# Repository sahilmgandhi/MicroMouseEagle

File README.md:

# MicroMouseEagle

MicroMouse eagle schematic and PCB Design for 2017 -> Sahil, Kyle, Vansh

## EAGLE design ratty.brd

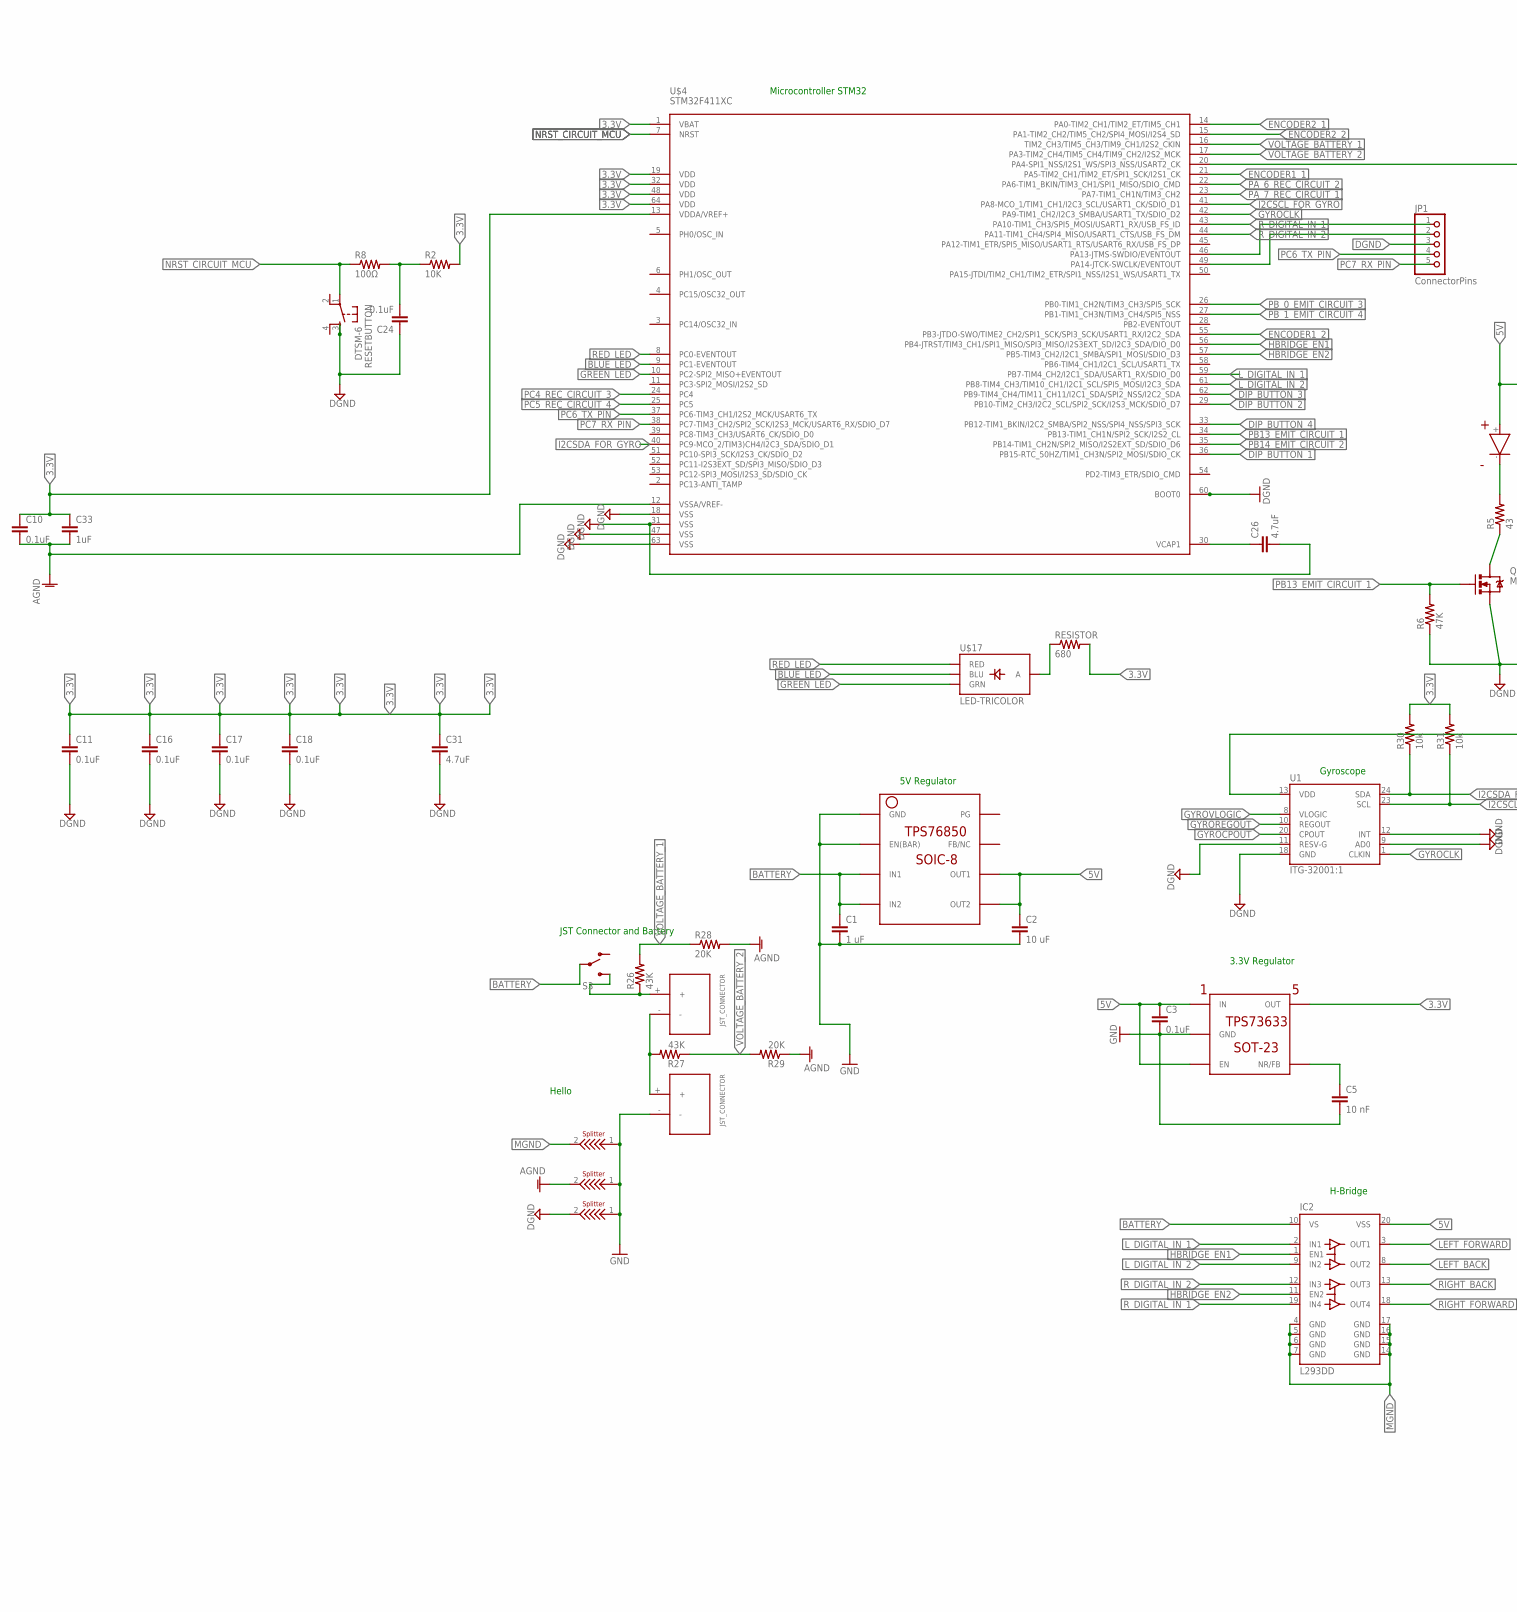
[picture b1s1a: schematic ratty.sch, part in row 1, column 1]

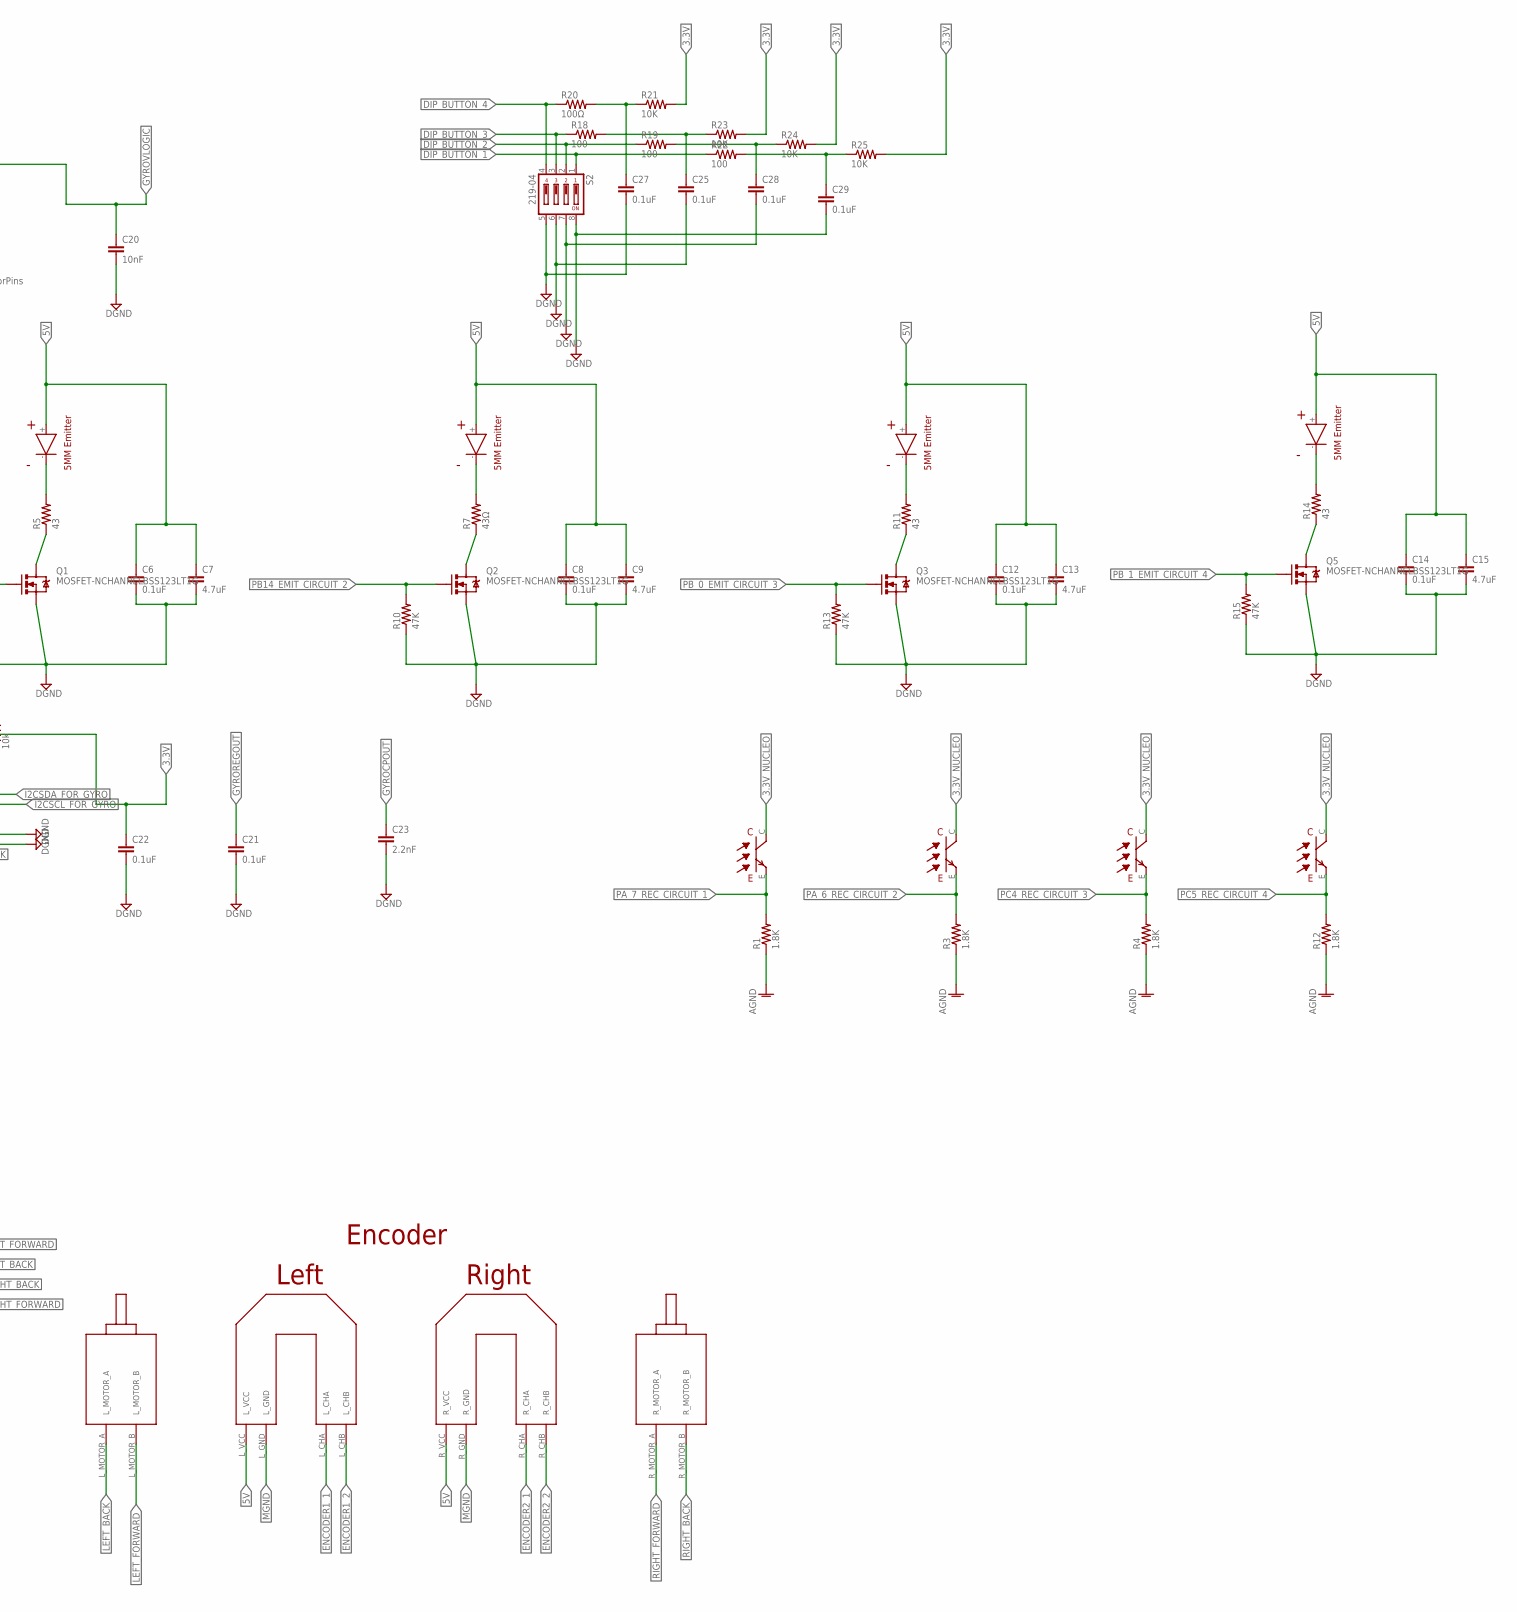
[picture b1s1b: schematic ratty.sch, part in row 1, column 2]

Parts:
A_SPLITTER: SPLITTER
C1: 1 uF; C0603
C2: 10 uF; C0603
C3, C6, C8, C10, C11, C12, C14, C16, C17, C18, C21, C22, C24, C25, C27, C28, C29: 0.1uF; C0603
C5: 10 nF; C0603
C7, C9, C13, C15, C26, C31: 4.7uF; C0603
C20: 10nF; C0603
C23: 2.2nF; C0603
C33: 1uF; C0603
D_SPLITTER: SPLITTER
IC2: L293DD; SO20
JP1: ConnectorPins; 1X05
M_SPLITTER: SPLITTER
Q1, Q2, Q3, Q5: MOSFET-NCHANNELBSS123LT1G; SOT23-3
R1, R3, R4, R12: 1.8K; R0603
R2, R21, R23, R24, R25: 10K; R0603
R5, R11, R14: 43; R1206
R6, R10, R13, R15: 47K; R0603
R7: 43Ω; R1206
R8, R20: 100Ω; R0603
R18, R19, R22: 100; R0603
R26, R27: 43K; R0603
R28, R29: 20K; R0603
R30, R31: 10k; R0603
RESETBUTTON: DTSM-6
RESISTOR: 680; R0603
S2: 219-04; CTS-219-04
S3: SWITCH-SPSTPTH; SWITCH-SPDT
U1: ITG-32001:1; QFN-24_ITG3200_1:1
U$1, U$2: JST_CONNECTOR_FEMALE
U$3: TPS76850(SOIC-8)
U$4: STM32F411XC; LQFP64
U$5: TPS73633(SOT-23)
U$6, U$9, U$11, U$13: RECEIVER
U$8: FUTURA_V1.0_MOTOR_MOUNT; FUTURA_V1.0_MOTOT_MOUNT
U$15, U$16, U$18, U$19: EMITTER
U$17: LED-TRICOLOR; LED-TRICOLOR-SMD

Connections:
3.3V: C10.1, C11.1, C16.1, C17.1, C18.1, C22.1, C31.1, C33.1, R2.2, R21.2, R23.2, R24.2, R25.2, R30.2, R31.2, RESISTOR.2, U1.13 (VDD), U$4.1 (VBAT), U$4.13 (VDDA/VREF+), U$4.19 (VDD), U$4.32 (VDD), U$4.48 (VDD), U$4.64 (VDD), U$5.OUT
3.3V_NUCLEO: U$6.C, U$9.C, U$11.C, U$13.C
5V: C2.1, C3.1, C6.1, C7.1, C8.1, C9.1, C12.1, C13.1, C14.1, C15.1, IC2.20 (VSS), U$3.OUT1, U$3.OUT2, U$5.EN, U$5.IN, U$8.L_VCC, U$8.R_VCC, U$15.+, U$16.+, U$18.+, U$19.+
AGND: A_SPLITTER.2, C10.2, C33.2, R1.1, R3.1, R4.1, R12.1, R28.2, R29.1, U$4.12 (VSSA/VREF-)
BATTERY: C1.1, IC2.10 (VS), S3.2, U$3.IN1, U$3.IN2
BATTERY_1: R26.1, S3.3 (S), U$1.+
BATTERY_2: R27.2, U$1.-, U$2.+
BLUE_LED: U$4.9 (PC1-EVENTOUT), U$17.B (BLU)
DGND: C6.2, C7.2, C8.2, C9.2, C11.2, C12.2, C13.2, C14.2, C15.2, C16.2, C17.2, C18.2, C20.2, C21.2, C22.2, C23.2, C24.1, C25.2, C26.2, C27.2, C28.2, C29.2, C31.2, D_SPLITTER.2, JP1.3, Q1.2 (S), Q2.2 (S), Q3.2 (S), Q5.2 (S), R6.1, R10.1, R13.1, R15.1, RESETBUTTON.3, RESETBUTTON.4, S2.5, S2.6, S2.7, S2.8, U1.9 (AD0), U1.11 (RESV-G), U1.12 (INT), U1.18 (GND), U$4.18 (VSS), U$4.31 (VSS), U$4.47 (VSS), U$4.60 (BOOT0), U$4.63 (VSS)
DIP_BUTTON_1: R22.1, S2.1, U$4.36 (PB15-RTC_50HZ/TIM1_CH3N/SPI2_MOSI/SDIO_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)
DIP_BUTTON_2: R19.1, S2.2, U$4.29 (PB10-TIM2_CH3/I2C2_SCL/SPI2_SCK/I2S3_MC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)
DIP_BUTTON_3: R18.1, S2.3, U$4.62 (PB9-TIM4_CH4/TIM11_CH11/I2C1_SDA/SPI2_N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)
DIP_BUTTON_4: R20.1, S2.4, U$4.33 (PB12-TIM1_BKIN/I2C2_SMBA/SPI2_NSS/SPI4_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)
ENCODER1_1: U$4.21 (PA5-TIM2_CH1/TIM2_ET/SPI1_SCK/I2S1_CK), U$8.L_CHA
ENCODER1_2: U$4.55 (PB3-JTDO-SWO/TIME2_CH2/SPI1_SCK/SPI3_SC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), U$8.L_CHB
ENCODER2_1: U$4.14 (PA0-TIM2_CH1/TIM2_ET/TIM5_CH1), U$8.R_CHA
ENCODER2_2: U$4.15 (PA1-TIM2_CH2/TIM5_CH2/SPI4_MOSI/I2S4_SD), U$8.R_CHB
GND: A_SPLITTER.1, C1.2, C2.2, C3.2, C5.2, D_SPLITTER.1, M_SPLITTER.1, U$2.-, U$3.EN(BAR), U$3.GND, U$5.GND
GREEN_LED: U$4.10 (PC2-SPI2_MISO+EVENTOUT), U$17.G (GRN)
GYROCLK: U1.1 (CLKIN), U$4.42 (PA9-TIM1_CH2/I2C3_SMBA/USART1_TX/SDIO_D2)
GYROCPOUT: C23.1, U1.20 (CPOUT)
GYROREGOUT: C21.1, U1.10 (REGOUT)
GYROVLOGIC: C20.1, U1.8 (VLOGIC), U$4.20 (PA4-SPI1_NSS/I2S1_WS/SPI3_NSS/USART2_CK)
HBRIDGE_EN1: IC2.1 (EN1), U$4.56 (PB4-JTRST/TIM3_CH1/SPI1_MISO/SPI3_MISO/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)
HBRIDGE_EN2: IC2.11 (EN2), U$4.57 (PB5-TIM3_CH2/I2C1_SMBA/SPI1_MOSI/SDIO_D3)
I2CSCL_FOR_GYRO: R31.1, U1.23 (SCL), U$4.41 (PA8-MCO_1/TIM1_CH1/I2C3_SCL/USART1_CK/S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)
I2CSDA_FOR_GYRO: R30.1, U1.24 (SDA), U$4.40 (PC9-MCO_2/TIM3)CH4/I2C3_SDA/SDIO_D1)
LED/R5: R5.2, U$15.-
LED/R7: R7.2, U$16.-
LED/R11: R11.2, U$18.-
LED/R14: R14.2, U$19.-
LEFT_BACK: IC2.8 (OUT2), U$8.L_MOTOR_A
LEFT_FORWARD: IC2.3 (OUT1), U$8.L_MOTOR_B
L_DIGITAL_IN_1: IC2.2 (IN1), U$4.59 (PB7-TIM4_CH2/I2C1_SDA/USART1_RX/SDIO_D0)
L_DIGITAL_IN_2: IC2.9 (IN2), U$4.61 (PB8-TIM4_CH3/TIM10_CH1/I2C1_SCL/SPI5_MO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)
MGND: IC2.4 (GND), IC2.5 (GND), IC2.6 (GND), IC2.7 (GND), IC2.14 (GND), IC2.15 (GND), IC2.16 (GND), IC2.17 (GND), M_SPLITTER.2, U$8.L_GND, U$8.R_GND
unnamed: RESISTOR.1, U$17.A
unnamed: C24.2, R2.1, R8.2
unnamed: JP1.1, U$4.46 (PA13-JTMS-SWDIO/EVENTOUT)
unnamed: JP1.2, U$4.49 (PA14-JTCK-SWCLK/EVENTOUT)
unnamed: C26.1, U$4.30 (VCAP1)
NRST_CIRCUIT_MCU: R8.1, RESETBUTTON.1, U$4.7 (NRST)
PA_6_REC_CIRCUIT_2: R3.2, U$4.22 (PA6-TIM1_BKIN/TIM3_CH1/SPI1_MISO/SDIO_C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), U$9.E
PA_7_REC_CIRCUIT_1: R1.2, U$4.23 (PA7-TIM1_CH1N/TIM3_CH2), U$6.E
PB13_EMIT_CIRCUIT_1: Q1.1 (G), R6.2, U$4.34 (PB13-TIM1_CH1N/SPI2_SCK/I2S2_CL)
PB14_EMIT_CIRCUIT_2: Q2.1 (G), R10.2, U$4.35 (PB14-TIM1_CH2N/SPI2_MISO/I2S2EXT_SD/SDI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)
PB_0_EMIT_CIRCUIT_3: Q3.1 (G), R13.2, U$4.26 (PB0-TIM1_CH2N/TIM3_CH3/SPI5_SCK)
PB_1_EMIT_CIRCUIT_4: Q5.1 (G), R15.2, U$4.27 (PB1-TIM1_CH3N/TIM3_CH4/SPI5_NSS)
PC4_REC_CIRCUIT_3: R4.2, U$4.24 (PC4), U$11.E
PC5_REC_CIRCUIT_4: R12.2, U$4.25 (PC5), U$13.E
PC6_TX_PIN: JP1.4, U$4.37 (PC6-TIM3_CH1/I2S2_MCK/USART6_TX)
PC7_RX_PIN: JP1.5, U$4.38 (PC7-TIM3_CH2/SPI2_SCK/I2S3_MCK/USART6_R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)
RED_LED: U$4.8 (PC0-EVENTOUT), U$17.R (RED)
RIGHT_BACK: IC2.13 (OUT3), U$8.R_MOTOR_B
RIGHT_FORWARD: IC2.18 (OUT4), U$8.R_MOTOR_A
R_DIGITAL_IN_1: IC2.19 (IN4), U$4.43 (PA10-TIM1_CH3/SPI5_MOSI/USART1_RX/USB_F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)
R_DIGITAL_IN_2: IC2.12 (IN3), U$4.44 (PA11-TIM1_CH4/SPI4_MISO/USART1_CTS/USB_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)
TO_C5_CAP: C5.1, U$5.NR/FB
TO_Q1_MOS: Q1.3 (D), R5.1
TO_Q2_MOS: Q2.3 (D), R7.1
TO_Q3_MOS: Q3.3 (D), R11.1
TO_Q5_MOS: Q5.3 (D), R14.1
TO_R18/C25: C25.1, R18.2, R23.1
TO_R19/C28: C28.1, R19.2, R24.1
TO_R20/C27: C27.1, R20.2, R21.1
TO_R22/C29: C29.1, R22.2, R25.1
VOLTAGE_BATTERY_1: R26.2, R28.1, U$4.16 (TIM2_CH3/TIM5_CH3/TIM9_CH1/I2S2_CKIN)
VOLTAGE_BATTERY_2: R27.1, R29.2, U$4.17 (PA3-TIM2_CH4/TIM5_CH4/TIM9_CH2/I2S2_MCK)

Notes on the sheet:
Hello
H-Bridge
3.3V Regulator
5V Regulator
JST Connector and Battery
Gyroscope
Microcontroller STM32

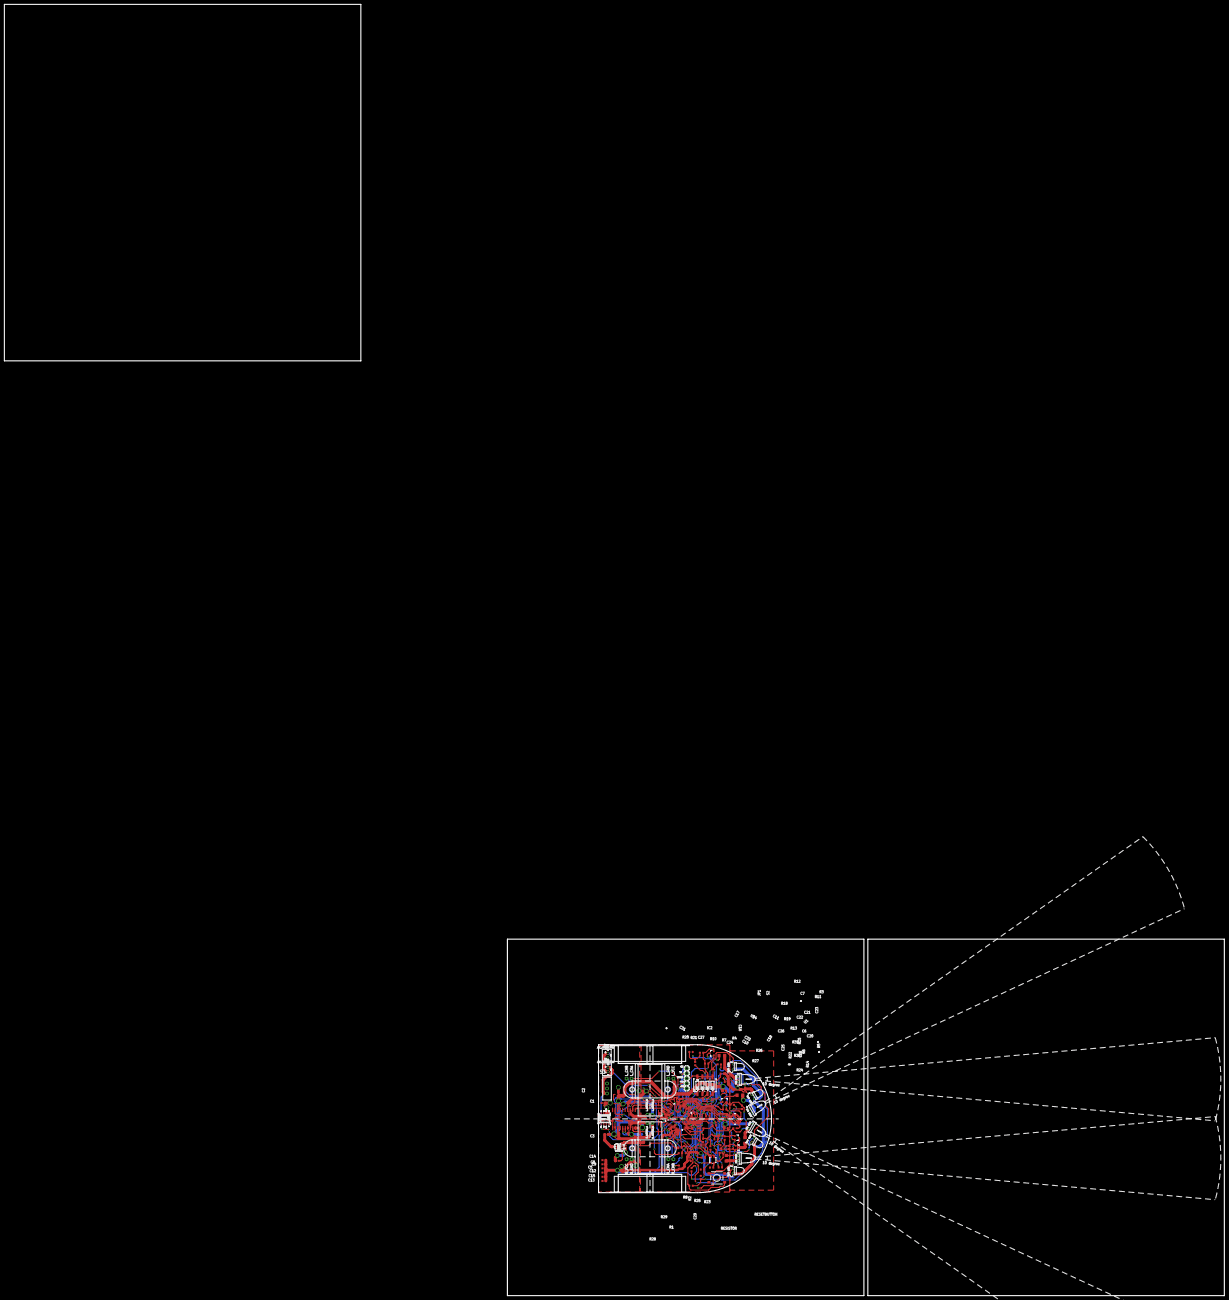
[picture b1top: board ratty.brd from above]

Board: 2 copper layers, 616.0 x 652.0 mm, 86 parts (0 on the bottom side), 68 nets.

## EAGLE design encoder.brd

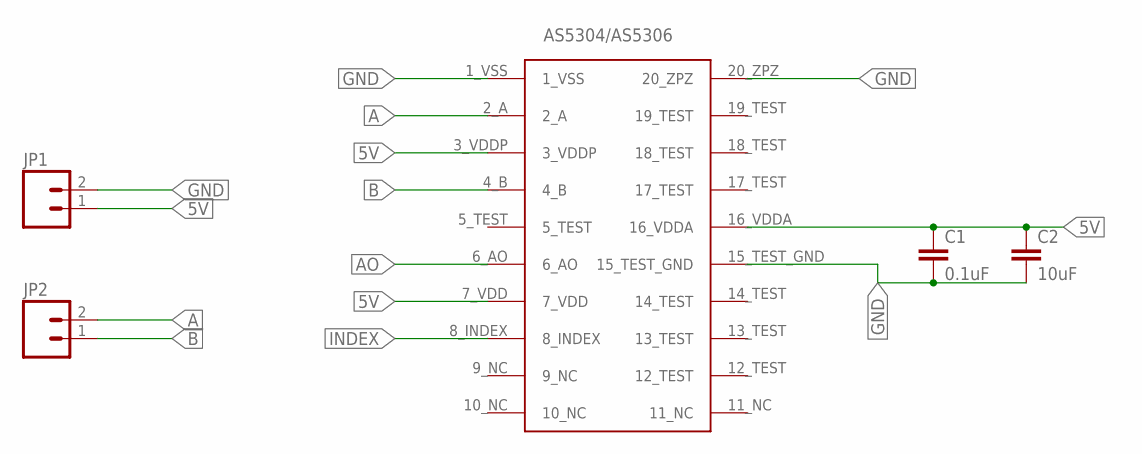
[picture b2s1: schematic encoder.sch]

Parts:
C1: 0.1uF; C0603
C2: 10uF; C0603
JP1, JP2: M02LOCK; 1X02_LOCK
U$1: AS5304/AS5306-ENCODER

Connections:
5V: C1.1, C2.1, JP1.1, U$1.3_VDDP, U$1.7_VDD, U$1.16_VDDA
A: JP2.2, U$1.2_A
AO: U$1.6_AO
B: JP2.1, U$1.4_B
GND: C1.2, C2.2, JP1.2, U$1.1_VSS, U$1.15_TEST_GND, U$1.20_ZPZ
INDEX: U$1.8_INDEX

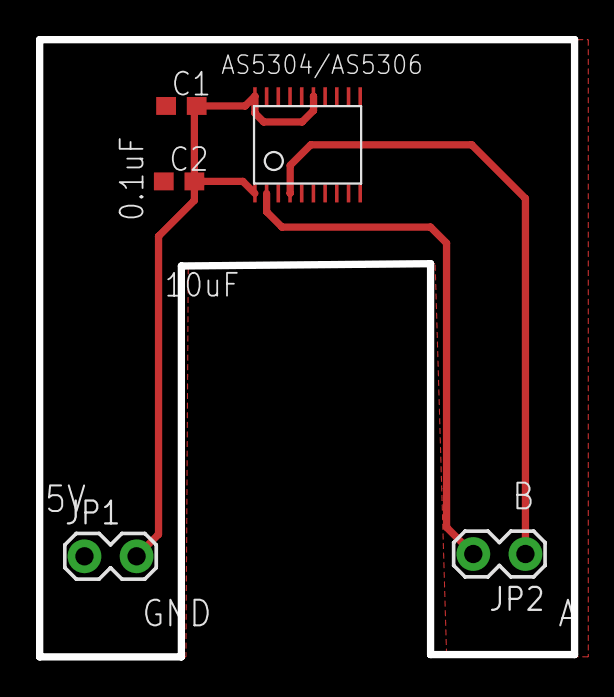
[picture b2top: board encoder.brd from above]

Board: 2 copper layers, 29.7 x 34.3 mm, 5 parts (0 on the bottom side), 4 nets.

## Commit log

2017-01-12 Added MCU, Added more LEDs, Added more Receivers, Removed Polulu Encoders
2017-01-13 Replaced footprints to SMD for all resistors and Capacitors
2017-01-13 Added gyro and some paths for MCU
2017-01-13 Resistor values updated
2017-01-14 Switched L239D to L239DD
2017-01-14 Updated some label names
2017-01-14 Added MCU related things
2017-01-14 Added gitignore file. Deleted # files
2017-01-15 Added gyro
2017-01-15 Changed labels according to what brandon said
2017-01-15 finished gyro according to Aravinds advice
2017-01-15 Added splitters before GNDS. GNDs still need to be renamed
2017-01-15 kek lol undid previous commit
2017-01-15 More of aravinds changes. almost done
2017-01-15 fixed 0.1uf error
2017-01-15 Added LEDs
2017-01-15 Added dip switches
2017-01-15 Adding battery check
2017-01-15 finished schematic yeee boiis
2017-01-15 Finished motor schematic and placed led/sensors on board
2017-01-16 Increased board size. Placed more components
2017-01-16 Placed all parts. Drew top and bot layers
2017-01-16 Named top and bot layers
2017-01-16 Fixed hbridge whoops
2017-01-16 Updated .gitignore. Added encoder module
2017-01-16 Updated gitignore
2017-01-16 Update cells
2017-01-16 Realigned side wall led & ir sensors to be symmetrical
2017-01-16 Routing started, renamed some unnamed parts.
2017-01-16 More routing, more naming
2017-01-16 Need to change capacitors, changed the switch
2017-01-16 Fixed the VDD and VSS of the MCU
2017-01-16 fixed more MCU
2017-01-16 Made board larger to incorporate switch
2017-01-16 Redid some of kyle's routes
2017-01-17 routing
2017-01-17 more routing
2017-01-17 Fixed errors in schematics
2017-01-17 latest changes
2017-01-17 once again time to reroute
2017-01-17 Routed 4 wires!!(not really)
2017-01-17 attempted some more routes
2017-01-17 first autoroute with 14 airwires left
2017-01-17 Changed schematic a bit to make it easier to route
2017-01-18 Moved components around
2017-01-18 Changed switch, resized, and added pours except AGND
2017-01-18 Routed left side
2017-01-18 Finished entire left side
2017-01-18 Finished some mistakes
2017-01-18 Routed gyro
2017-01-18 routed right and thinngs to the outside and working my way in
2017-01-18 Fixed widths of some power routes
2017-01-18 I need to pay attention in cs 111
2017-01-18 Did one side of MCU
2017-01-18 Down to 29 airwires boiiis
2017-01-18 Routed some more
2017-01-18 Almost done
2017-01-19 1 airwire left
2017-01-19 Finished
2017-01-20 Beginning to work on fixing up the mouse
2017-01-22 Ripped left side up
2017-01-22 Changed IR and changing LED
2017-01-22 GOGOGO
2017-01-22 more changes except for the board
2017-01-22 Some stuff
2017-01-23 routed some of the wires
2017-01-23 Removed unncessary routes
2017-01-24 Finished h bridge and others, 11 wires left
2017-01-24 deleted polygon and 10 wires
2017-01-25 Get rid of some unecessary wires
2017-01-26 Dunzo 0 airwires
2017-01-26 Pour more pours
2017-01-27 Sahil this is yours
2017-01-27 Moved vias, we need to change size of gnds now??
2017-01-27 3.3v for u kylio
2017-01-27 I guess we're done
2017-01-27 Need to smash and label everything
2017-01-27 Moving names off and positioning labels
2017-01-27 Looks good
2017-01-27 Someone lied to me
2017-01-27 We done boiiss
2017-01-28 Made things thick
2017-02-21 Fixed button issue

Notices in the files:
parts and their libraries:
SparkFun: Licensing: CC v3.0 Share-Alike You are welcome to use this library for commercial purposes.
SparkFun-Sensors: Licensing: Creative Commons ShareAlike 4.0 International - https://creativecommons.org/licenses/by-sa/4.0
